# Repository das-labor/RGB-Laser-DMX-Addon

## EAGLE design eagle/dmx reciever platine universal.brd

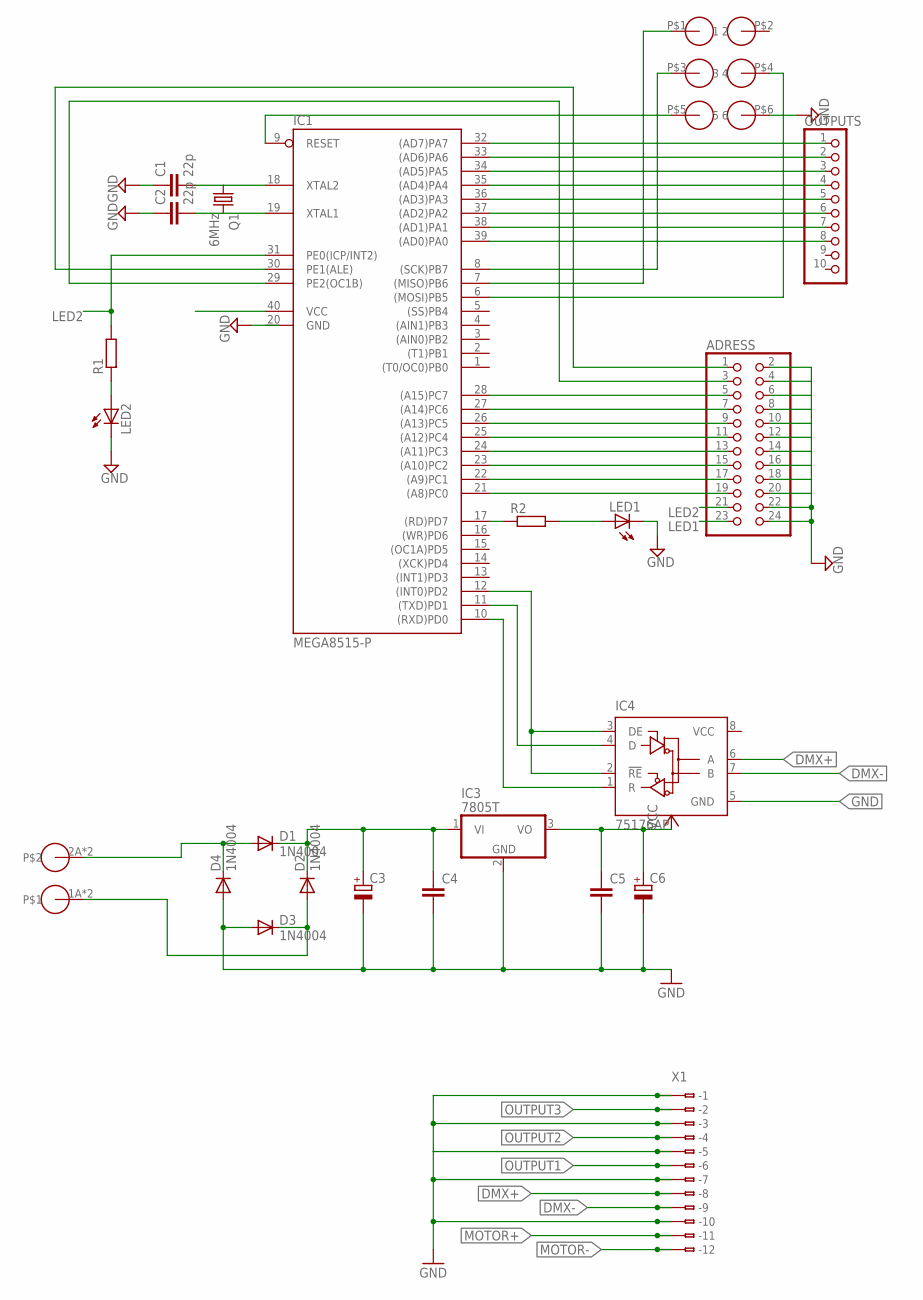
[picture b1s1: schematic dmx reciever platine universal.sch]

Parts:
ADRESS: PINHD-2X12; 2X12
C1, C2: 22p; C025-024X044
C3, C6: CPOL-EUE3.5-8; E3,5-8
C4, C5: C-EU025-024X044; C025-024X044
D1, D2, D3, D4: 1N4004; DO41-10
IC1: MEGA8515-P; DIL40
IC3: 7805T; TO220H
IC4: 75176AP; DIL08
ISP: 2X3
LED1, LED2: LEDCHIP-LED0805; CHIP-LED0805
OUTPUTS: PINHD-1X10; 1X10
Q1: 6MHz; HC49/S
R1, R2: R-EU_M0805; M0805
U$1: WAGO20602POL; WAGO20602PIN
X1: 233-112

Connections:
DMX+: IC4.6 (A), X1.A8 (-8), X1.B8 (B-8)
DMX-: IC4.7 (B), X1.A9 (-9), X1.B9 (B-9)
GND: ADRESS.2, ADRESS.4, ADRESS.6, ADRESS.8, ADRESS.10, ADRESS.12, ADRESS.14, ADRESS.16, ADRESS.18, ADRESS.20, ADRESS.22, ADRESS.24, C1.1, C2.1, C3.-, C4.2, C5.2, C6.-, D3.A, D4.A, IC1.20 (GND), IC3.2 (GND), IC4.5 (GND), ISP.P$6 (6), LED1.C, LED2.C, X1.A1 (-1), X1.A3 (-3), X1.A5 (-5), X1.A7 (-7), X1.A10 (-10), X1.B1 (B-1), X1.B3 (B-3), X1.B5 (B-5), X1.B7 (B-7), X1.B10 (B-10)
LED1: ADRESS.23, IC1.17 ((RD)PD7), R2.1
LED2: ADRESS.21, IC1.31 (PE0(ICP/INT2)), R1.2
MOTOR+: X1.A11 (-11), X1.B11 (B-11)
MOTOR-: X1.A12 (-12), X1.B12 (B-12)
unnamed: C2.2, IC1.19 (XTAL1), Q1.2
unnamed: C1.2, IC1.18 (XTAL2), Q1.1
unnamed: ADRESS.5, IC1.28 ((A15)PC7)
unnamed: ADRESS.7, IC1.27 ((A14)PC6)
unnamed: ADRESS.15, IC1.23 ((A10)PC2)
unnamed: ADRESS.9, IC1.26 ((A13)PC5)
unnamed: ADRESS.11, IC1.25 ((A12)PC4)
unnamed: ADRESS.13, IC1.24 ((A11)PC3)
unnamed: LED2.A, R1.1
unnamed: ADRESS.17, IC1.22 ((A9)PC1)
unnamed: ADRESS.3, IC1.29 (PE2(OC1B))
unnamed: ADRESS.1, IC1.30 (PE1(ALE))
unnamed: IC1.9 (RESET), ISP.P$5 (5)
unnamed: IC1.8 ((SCK)PB7), ISP.P$3 (3)
unnamed: IC1.7 ((MISO)PB6), ISP.P$1 (1)
unnamed: IC1.6 ((MOSI)PB5), ISP.P$4 (4)
unnamed: IC1.10 ((RXD)PD0), IC4.1 (R)
unnamed: IC1.12 ((INT0)PD2), IC4.2 (!RE), IC4.3 (DE)
unnamed: IC1.11 ((TXD)PD1), IC4.4 (D)
unnamed: ADRESS.19, IC1.21 ((A8)PC0)
unnamed: LED1.A, R2.2
unnamed: D1.A, D4.C, U$1.2A, U$1.2B
unnamed: D2.A, D3.C, U$1.1A, U$1.1B
unnamed: C3.+, C4.1, D1.C, D2.C, IC3.1 (VI)
OUTPUT1: IC1.32 ((AD7)PA7), OUTPUTS.1, X1.A6 (-6), X1.B6 (B-6)
OUTPUT2: IC1.33 ((AD6)PA6), OUTPUTS.2, X1.A4 (-4), X1.B4 (B-4)
OUTPUT3: IC1.34 ((AD5)PA5), OUTPUTS.3, X1.A2 (-2), X1.B2 (B-2)
OUTPUT4: IC1.35 ((AD4)PA4), OUTPUTS.4
OUTPUT5: IC1.36 ((AD3)PA3), OUTPUTS.5
OUTPUT6: IC1.37 ((AD2)PA2), OUTPUTS.6
OUTPUT7: IC1.38 ((AD1)PA1), OUTPUTS.7
OUTPUT8: IC1.39 ((AD0)PA0), OUTPUTS.8
VCC: C5.1, C6.+, IC1.40 (VCC), IC3.3 (VO), IC4.8 (VCC)

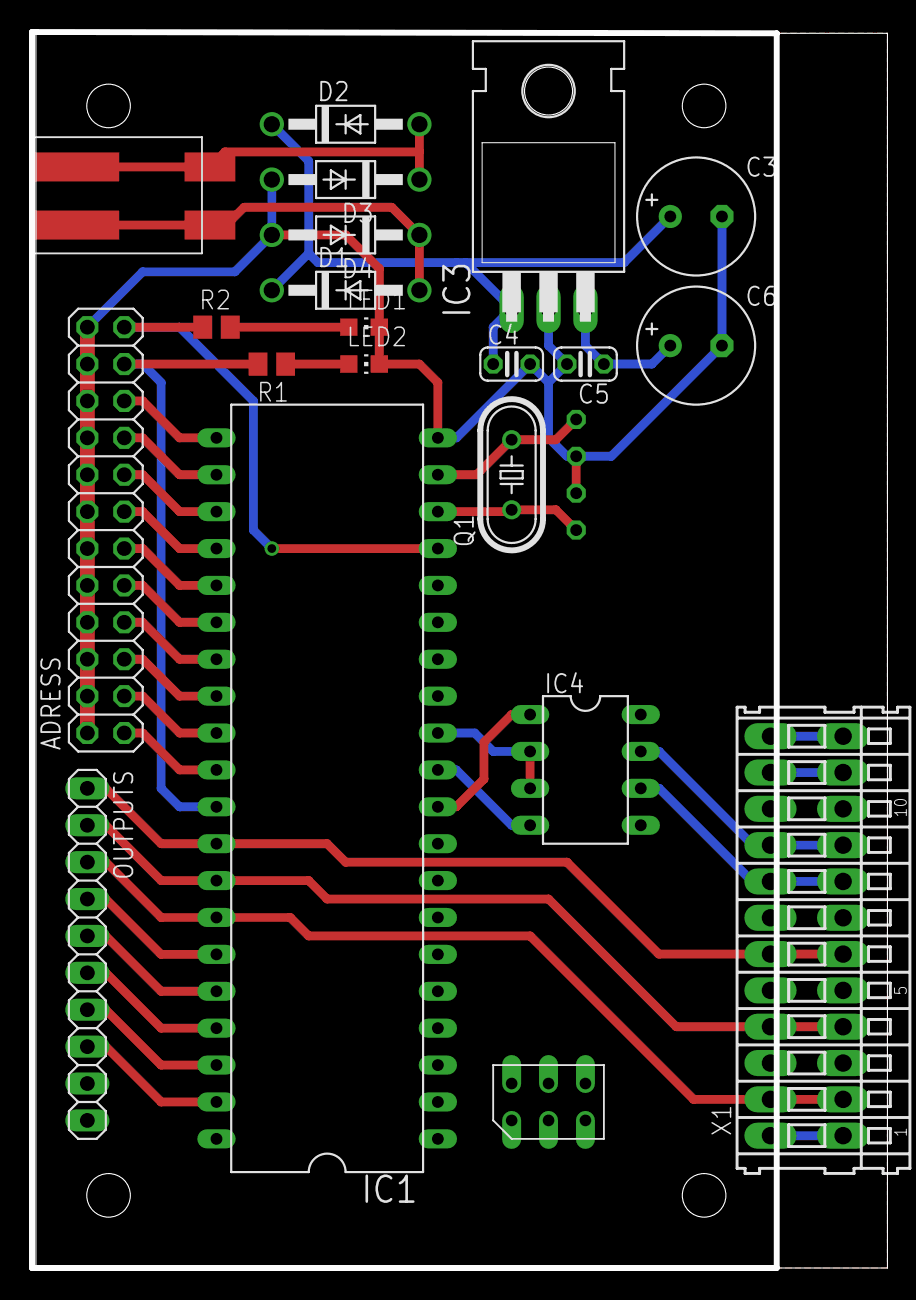
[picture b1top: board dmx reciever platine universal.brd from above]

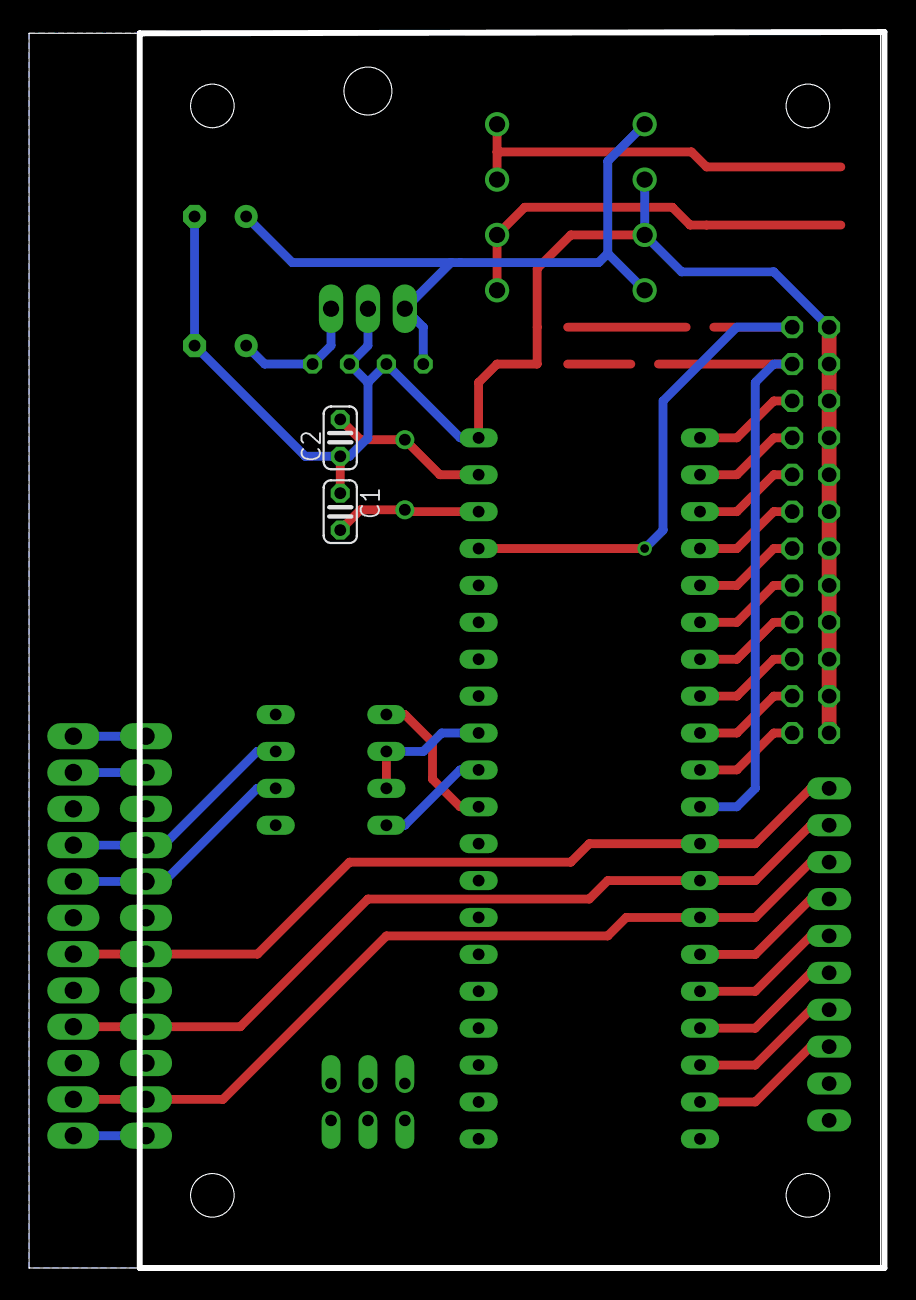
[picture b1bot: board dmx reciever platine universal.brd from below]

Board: 2 copper layers, 58.7 x 85.1 mm, 23 parts (2 on the bottom side), 40 nets.

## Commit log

2015-05-26 new output connector
